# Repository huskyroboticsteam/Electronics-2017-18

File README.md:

# Electronics-2017-18

This is the 2017-18 Husky Robotics repository for electronics board designs and everything else electronics!

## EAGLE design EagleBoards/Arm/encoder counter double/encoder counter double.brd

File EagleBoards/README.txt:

Folder for the HRT Eagle library, Eagle Boards

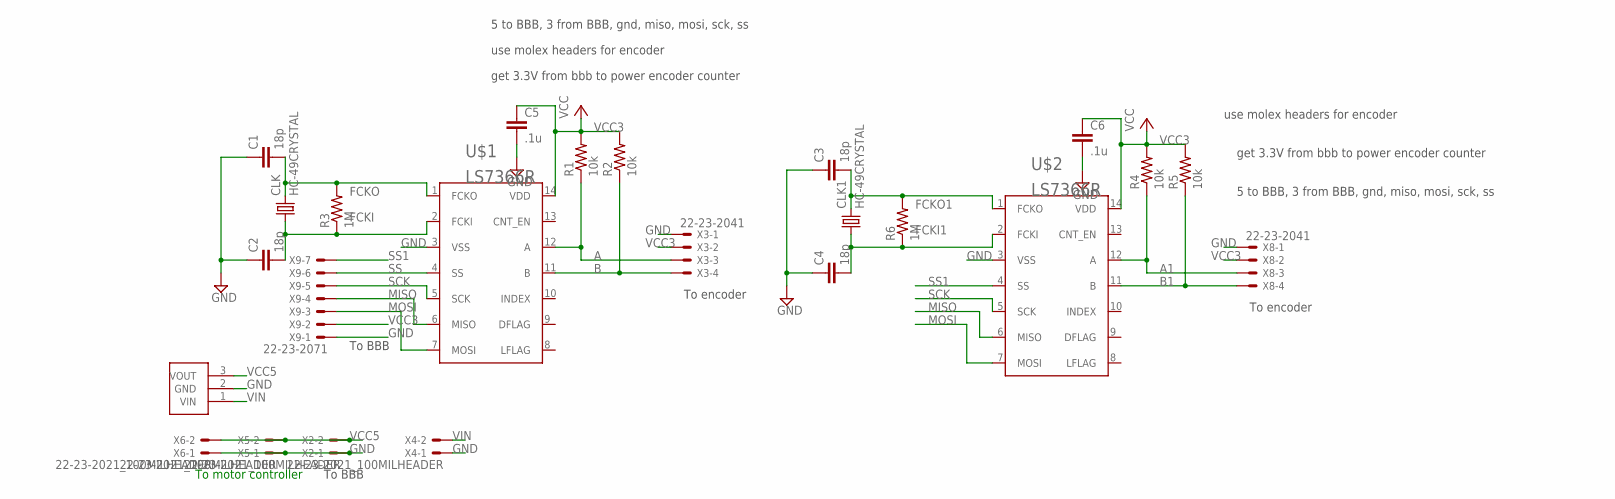
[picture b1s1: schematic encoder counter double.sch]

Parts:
C1, C2, C3, C4: 18p; C1206
C5, C6: .1u; C1206
CLK, CLK1: HC-49CRYSTAL; HC49/S
R1, R2, R4, R5: 10k; R1206
R3, R6: 1M; R1206
U$1, U$2: LS7366R; SO14
U$3: OKI-78SR-X_3PIN-DCDC; MA03-1
X2, X4, X5, X6: 22-23-2021_100MILHEADER; 22-23-2021_199MILHEADER
X3, X8: 22-23-2041
X9: 22-23-2071

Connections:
A: R1.1, U$1.12 (A), X3.3
A1: R4.1, U$2.12 (A), X8.3
B: R2.1, U$1.11 (B), X3.4
B1: R5.1, U$2.11 (B), X8.4
FCKI: C2.2, CLK.1, R3.1, U$1.2 (FCKI)
FCKI1: C4.2, CLK1.1, R6.1, U$2.2 (FCKI)
FCKO: C1.2, CLK.2, R3.2, U$1.1 (FCKO)
FCKO1: C3.2, CLK1.2, R6.2, U$2.1 (FCKO)
GND: C1.1, C2.1, C3.1, C4.1, C5.2, C6.2, U$1.3 (VSS), U$2.3 (VSS), U$3.2 (GND), X2.1, X3.1, X4.1, X5.1, X6.1, X8.1, X9.1
MISO: U$1.6 (MISO), U$2.6 (MISO), X9.4
MOSI: U$1.7 (MOSI), U$2.7 (MOSI), X9.3
SCK: U$1.5 (SCK), U$2.5 (SCK), X9.5
SS: U$1.4 (SS), X9.6
SS1: U$2.4 (SS), X9.7
VCC3: C5.1, C6.1, R1.2, R2.2, R4.2, R5.2, U$1.14 (VDD), U$2.14 (VDD), X3.2, X8.2, X9.2
VCC5: U$3.3 (VOUT), X2.2, X5.2, X6.2
VIN: U$3.1 (VIN), X4.2

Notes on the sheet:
use molex headers for encoder
get 3.3V from bbb to power encoder counter
5 to BBB, 3 from BBB, gnd, miso, mosi, sck, ss
To BBB
To encoder
To motor controller

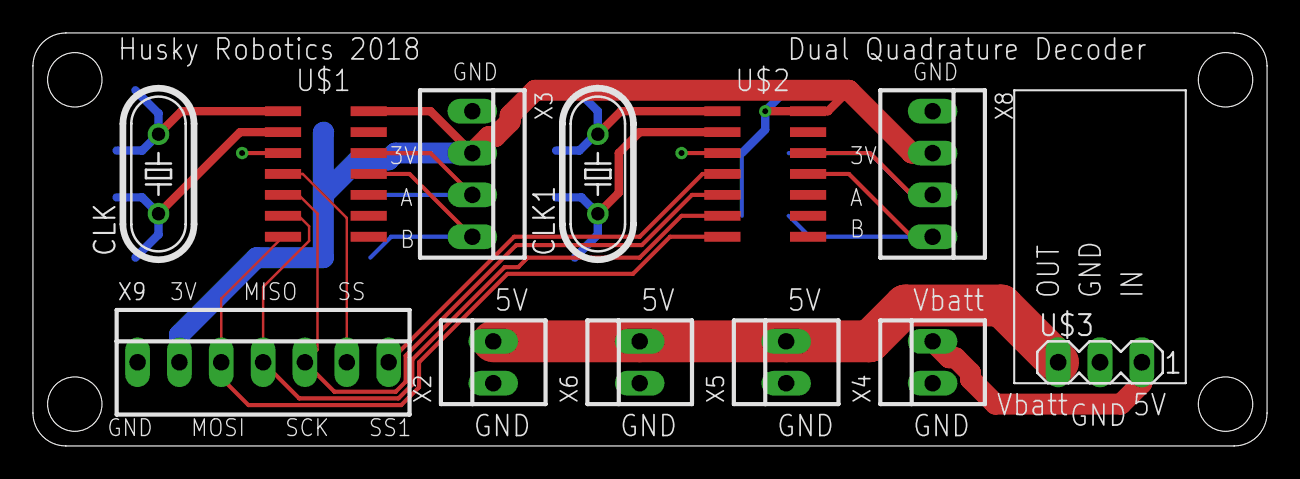
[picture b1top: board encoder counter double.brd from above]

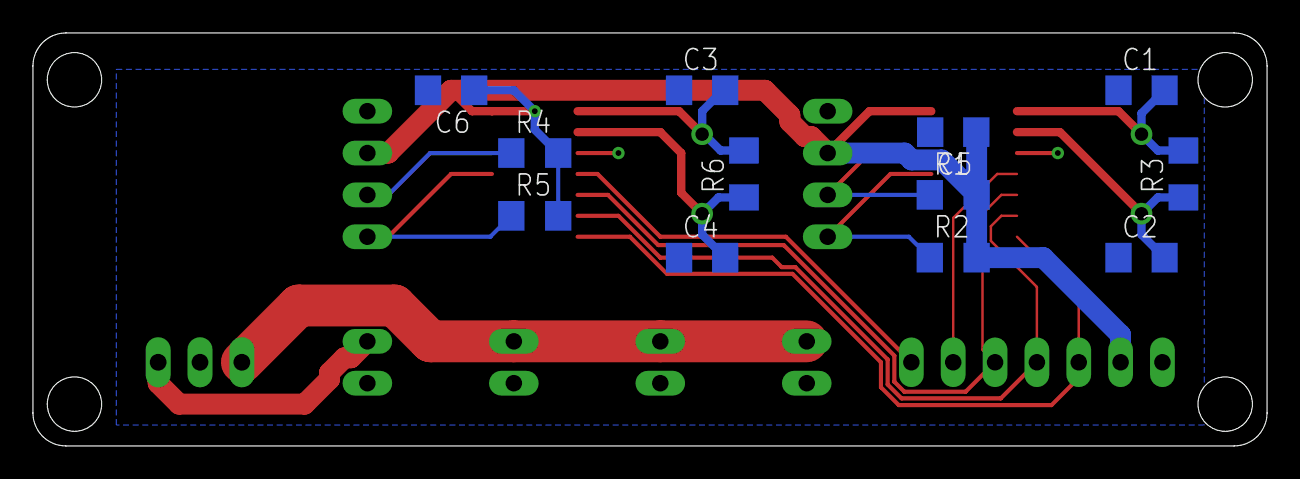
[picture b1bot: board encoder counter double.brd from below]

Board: 2 copper layers, 74.9 x 25.1 mm, 24 parts (12 on the bottom side), 17 nets.

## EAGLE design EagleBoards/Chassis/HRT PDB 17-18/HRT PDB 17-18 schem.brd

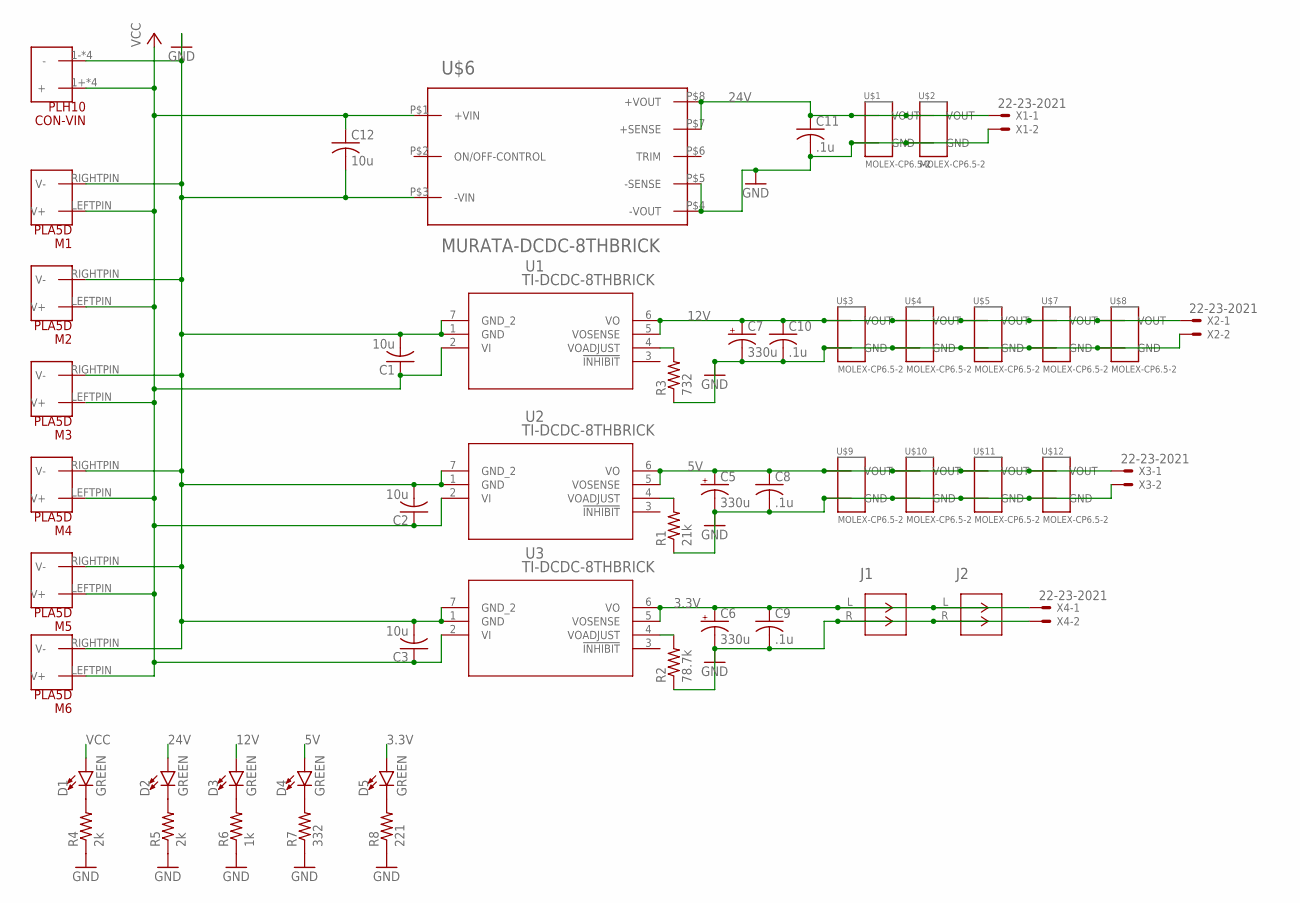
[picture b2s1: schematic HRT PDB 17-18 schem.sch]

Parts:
C1, C2, C3, C12: 10u; C1210
C5, C6, C7: 330u; E5-10,5
C8, C9, C10, C11: .1u; C0603
CON-VIN: PLH10; PLH10PCKG
D1, D2, D3, D4, D5: GREEN; LED-0603
J1, J2: TE-TERM-BLOCK
M1, M2, M3, M4, M5, M6: PLA5D; PLA5PACK
R1: 21k; R0603
R2: 78.7k; R0603
R3: 732; R0603
R4, R5: 2k; R0805
R6: 1k; R0805
R7: 332; R0805
R8: 221; R0805
U1, U2, U3: TI-DCDC-8THBRICK; TIBRICK
U$1, U$2, U$3, U$4, U$5, U$7, U$8, U$9, U$10, U$11, U$12: MOLEX-CP6.5-2; 151048-X2XX
U$6: MURATA-DCDC-8THBRICK; MURATA-8THBRICK
X1, X2, X3, X4: 22-23-2021

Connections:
3.3V: C6.+, C9.1, D5.A, J1.L (1), J2.L (1), U3.5 (VOSENSE), U3.6 (VO), X4.1
5V: C5.+, C8.1, D4.A, U2.5 (VOSENSE), U2.6 (VO), U$9.VOUT, U$10.VOUT, U$11.VOUT, U$12.VOUT, X3.1
12V: C7.+, C10.1, D3.A, U1.5 (VOSENSE), U1.6 (VO), U$3.VOUT, U$4.VOUT, U$5.VOUT, U$7.VOUT, U$8.VOUT, X2.1
24V: C11.1, D2.A, U$1.VOUT, U$2.VOUT, U$6.P$7 (+SENSE), U$6.P$8 (+VOUT), X1.1
GND: C1.2, C2.2, C3.2, C5.-, C6.-, C7.-, C8.2, C9.2, C10.2, C11.2, C12.2, CON-VIN.1- (-), CON-VIN.2- (-), CON-VIN.3- (-), CON-VIN.4- (-), J1.R (2), J2.R (2), M1.RIGHTPIN (V-), M2.RIGHTPIN (V-), M3.RIGHTPIN (V-), M4.RIGHTPIN (V-), M5.RIGHTPIN (V-), M6.RIGHTPIN (V-), R1.1, R2.1, R3.1, R4.1, R5.1, R6.1, R7.1, R8.1, U1.1 (GND), U1.7 (GND_2), U2.1 (GND), U2.7 (GND_2), U3.1 (GND), U3.7 (GND_2), U$1.GND, U$2.GND, U$3.GND, U$4.GND, U$5.GND, U$6.P$3 (-VIN), U$6.P$4 (-VOUT), U$6.P$5 (-SENSE), U$7.GND, U$8.GND, U$9.GND, U$10.GND, U$11.GND, U$12.GND, X1.2, X2.2, X3.2, X4.2
unnamed: D1.C, R4.2
unnamed: D2.C, R5.2
unnamed: R2.2, U3.4 (VOADJUST)
unnamed: R3.2, U1.4 (VOADJUST)
unnamed: R1.2, U2.4 (VOADJUST)
unnamed: D3.C, R6.2
unnamed: D4.C, R7.2
unnamed: D5.C, R8.2
VCC: C1.1, C2.1, C3.1, C12.1, CON-VIN.1+ (+), CON-VIN.2+ (+), CON-VIN.3+ (+), CON-VIN.4+ (+), D1.A, M1.LEFTPIN (V+), M2.LEFTPIN (V+), M3.LEFTPIN (V+), M4.LEFTPIN (V+), M5.LEFTPIN (V+), M6.LEFTPIN (V+), U1.2 (VI), U2.2 (VI), U3.2 (VI), U$6.P$1 (+VIN)

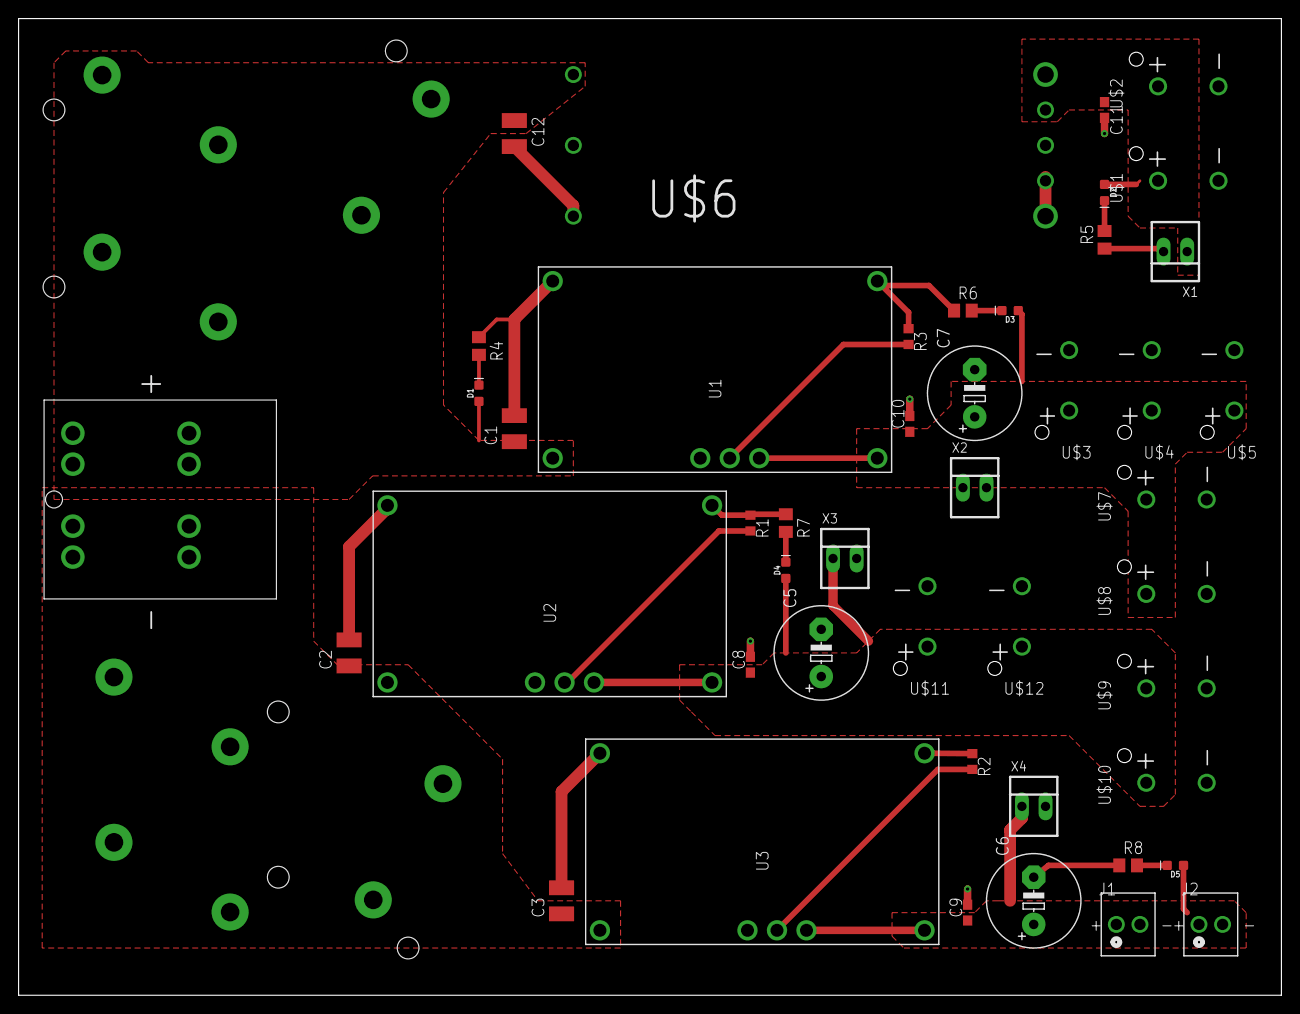
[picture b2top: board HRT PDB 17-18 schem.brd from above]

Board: 2 copper layers, 135.9 x 105.1 mm, 52 parts (0 on the bottom side), 14 nets.

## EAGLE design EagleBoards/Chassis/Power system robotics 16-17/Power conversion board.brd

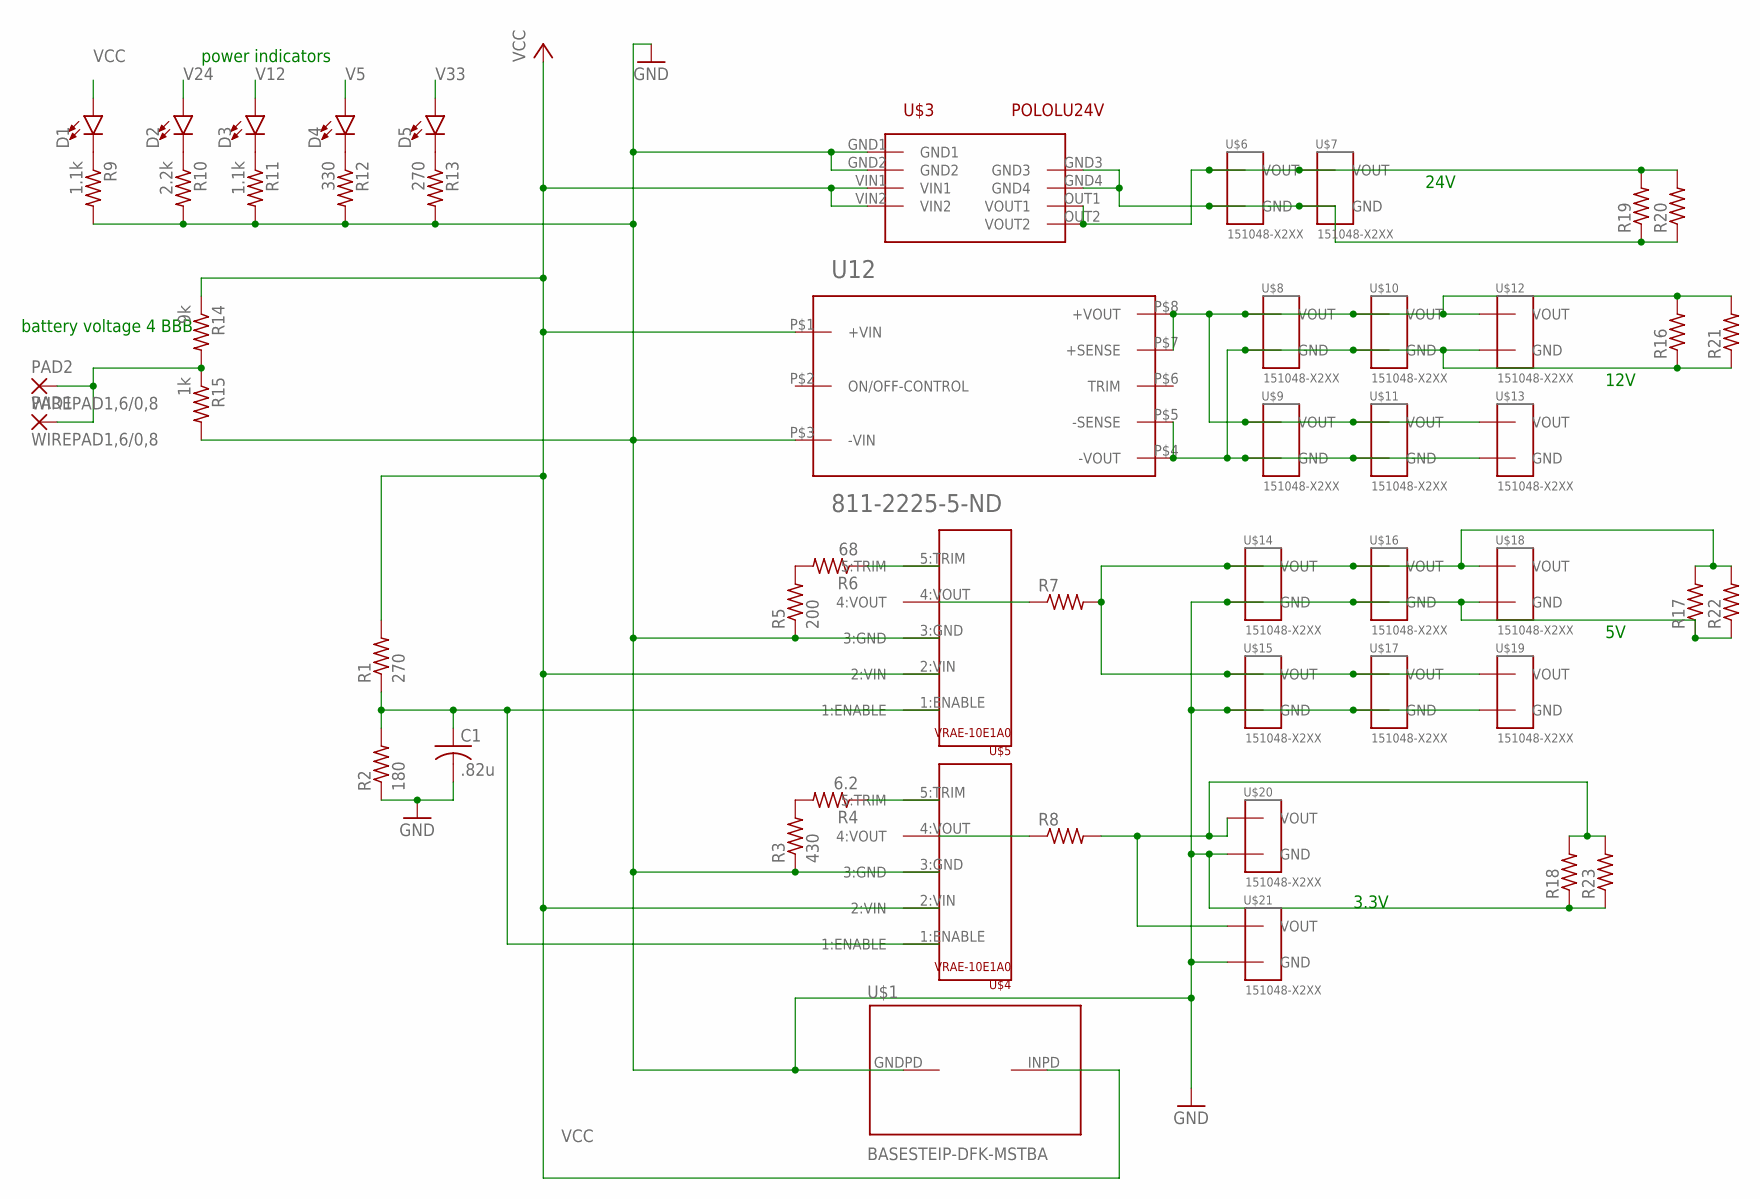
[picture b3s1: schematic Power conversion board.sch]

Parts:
C1: .82u; C0603
D1, D2, D3, D4, D5: LED5MM; LED_5MM
PAD1, PAD2: WIREPAD1,6/0,8; 1,6/0,8
R1, R13: 270; R0603
R2: 180; R0603
R3: 430; R0603
R4: 6.2; R0603
R5: 200; R0603
R6: 68; R0603
R7, R8, R16, R17, R18, R19, R20, R21, R22, R23: R-US_0204/5; 00PTCPACKAGE
R9, R11: 1.1k; R0603
R10: 2.2k; R0603
R12: 330; R0603
R14: 9k; R0603
R15: 1k; R0603
U12: 811-2225-5-ND
U$1: BASESTEIP-DFK-MSTBA; BASESTRIP-DFK-MSTBA
U$3: POLOLU24V; POLOLU24
U$4, U$5: VRAE-10E1A0; BEL_VRAE-10E1A0
U$6, U$7, U$8, U$9, U$10, U$11, U$12, U$13, U$14, U$15, U$16, U$17, U$18, U$19, U$20, U$21: 151048-X2XX

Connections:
GND: C1.2, R2.1, R3.1, R5.1, R9.2, R10.2, R11.2, R12.2, R13.2, R15.2, R16.1, R17.1, R18.1, R19.1, R20.1, R21.1, R22.1, R23.1, U12.P$3 (-VIN), U12.P$4 (-VOUT), U12.P$5 (-SENSE), U$1.GNDPD, U$3.GND1, U$3.GND2, U$3.GND3, U$3.GND4, U$4.3:GND, U$5.3:GND, U$6.GND, U$7.GND, U$8.GND, U$9.GND, U$10.GND, U$11.GND, U$12.GND, U$13.GND, U$14.GND, U$15.GND, U$16.GND, U$17.GND, U$18.GND, U$19.GND, U$20.GND, U$21.GND
unnamed: C1.1, R1.1, R2.2, U$4.1:ENABLE, U$5.1:ENABLE
unnamed: R3.2, R4.2
unnamed: R4.1, U$4.5:TRIM
unnamed: R5.2, R6.2
unnamed: R6.1, U$5.5:TRIM
unnamed: PAD1.1, PAD2.1, R14.2, R15.1
unnamed: R8.1, U$4.4:VOUT
unnamed: R7.1, U$5.4:VOUT
unnamed: D1.K (C), R9.1
unnamed: D2.K (C), R10.1
unnamed: D3.K (C), R11.1
unnamed: D4.K (C), R12.1
unnamed: D5.K (C), R13.1
V5: D4.A, R7.2, R17.2, R22.2, U$14.VOUT, U$15.VOUT, U$16.VOUT, U$17.VOUT, U$18.VOUT, U$19.VOUT
V12: D3.A, R16.2, R21.2, U12.P$7 (+SENSE), U12.P$8 (+VOUT), U$8.VOUT, U$9.VOUT, U$10.VOUT, U$11.VOUT, U$12.VOUT, U$13.VOUT
V24: D2.A, R19.2, R20.2, U$3.OUT1 (VOUT1), U$3.OUT2 (VOUT2), U$6.VOUT, U$7.VOUT
V33: D5.A, R8.2, R18.2, R23.2, U$20.VOUT, U$21.VOUT
VCC: D1.A, R1.2, R14.1, U12.P$1 (+VIN), U$1.INPD, U$3.VIN1, U$3.VIN2, U$4.2:VIN, U$5.2:VIN

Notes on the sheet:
power indicators
battery voltage 4 BBB
24V
12V
3.3V

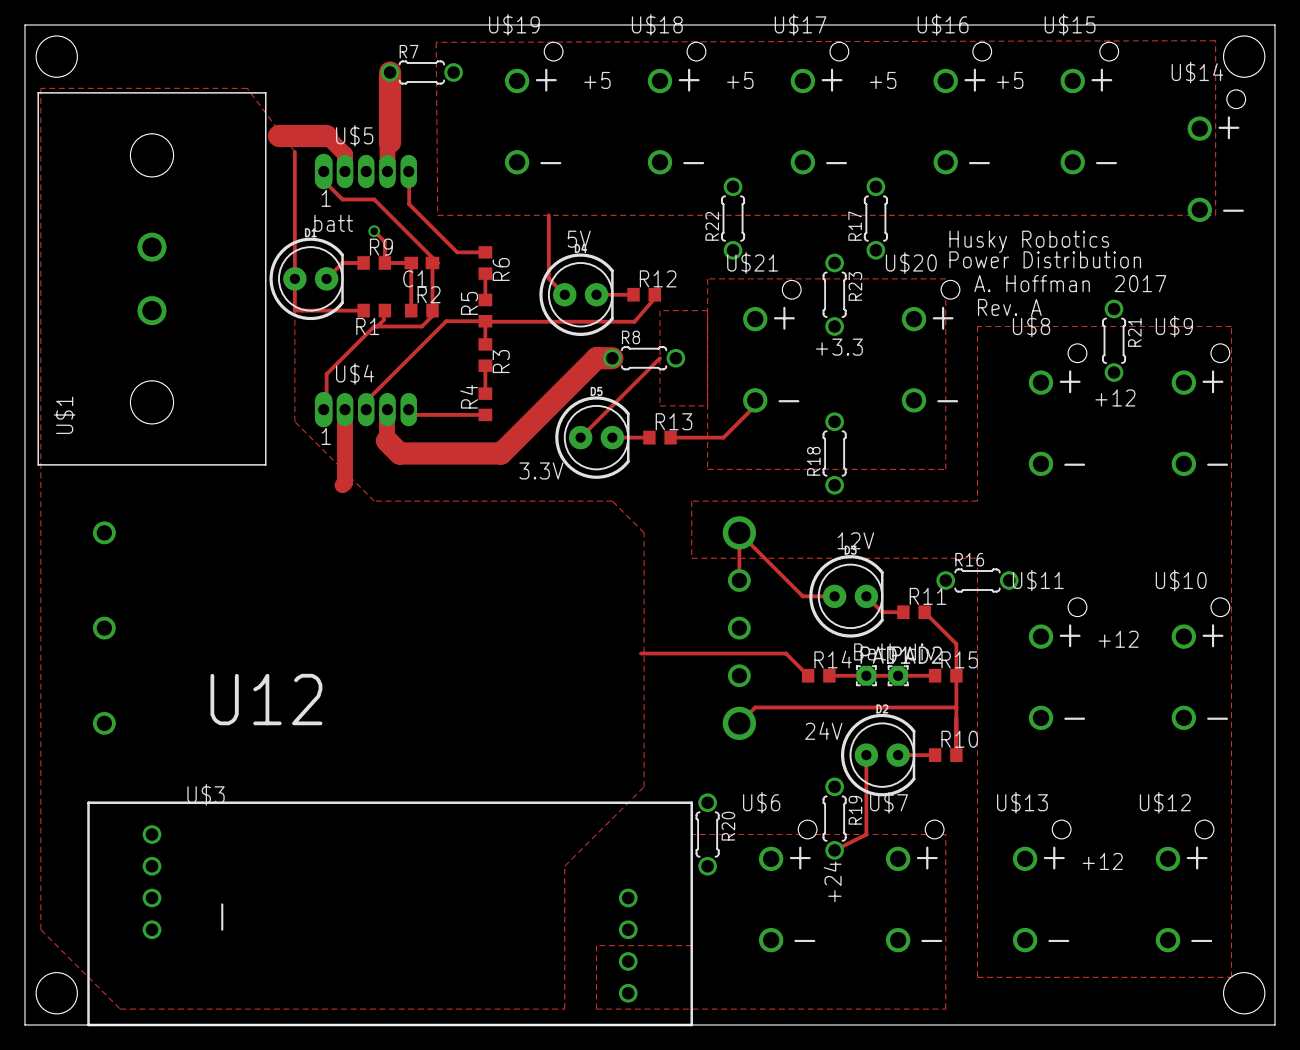
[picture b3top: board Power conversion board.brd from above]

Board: 2 copper layers, 100.0 x 80.0 mm, 52 parts (0 on the bottom side), 19 nets.

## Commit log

2017-12-02 Added empty readme
2017-12-02 Added existing Science designs.
2017-12-02 added Eagle folder
2017-12-02 Added Servo outputs
    Removed Encoder debouncing
2017-12-02 Actually saved this time
2017-12-02 Merged KiCad Libraries
    Now we have one "sciencelib" instead of 3. Releavnt changes made in schematics.
2017-12-02 Changed labelling standard for main board
2017-12-02 Current sensing on power board
2017-12-03 added eagle lbrs
2017-12-05 Added power pinouts and servo connections
2017-12-08 eagle lbr updates
2017-12-09 Changed LS7366R implementation per spec
2017-12-10 eagle gps
2017-12-23 chassis PDB in layout
2017-12-23 PDB mid dev
2017-12-23 pdb rev a
2018-01-07 Added sensor connections
2018-01-07 Added TLV2544ID to library
2018-01-07 Added ADC to main board schematic
2018-01-07 Updated schematic with new ADC layout
2018-01-07 Aded PWM device to schematic
2018-01-10 Adding component values, system current sensor
2018-01-12 Added decoupling capacitors, started component associatons, added RGB LEDs
2018-01-12 Cleaning up schematic, adding I2C test connector
2018-01-13 Fixing various board issues
    Decoupling caps, power connector, sensor connectors, power LEDs, etc.
2018-01-13 Added IC datasheets
2018-01-13 Added cable connector datasheets
2018-01-13 Fixed issues
2018-01-13 Added missing pullup
2018-01-13 Added optocouplers to servo outputs
2018-01-13 Fixed optocoupler
2018-01-13 Added connectors
2018-01-13 Added 7.2V regulator
2018-01-13 Schematic cleanup
2018-01-13 Switched to resistor networks for RGB LEDs
2018-01-13 Began Main board layout
2018-01-13 Continued working on main PCB
2018-01-14 Added BAC connectors to library
2018-01-14 Added RPi and Crystal Footprints
2018-01-14 Fixed RPi Footprint
    Someone (me) got the outline flipped...
2018-01-14 Added RGB LED footprint, working on layout
2018-01-14 Working on PCB
2018-01-14 Continuing PCB some more
2018-01-14 Began Power Board layout
2018-01-14 Added heatsink footprint
2018-01-14 Continued continuing on main board
2018-01-14 Updated footprint library
2018-01-14 "Finished routing"
    Except not really because it sucks
2018-01-14 Final PDB changes for tonight
2018-01-14 Last schematic changes for the night
2018-01-14 Finishing up for tonight.
2018-01-14 Changed layout again
    Could definitely still use some work...
2018-01-14 Finished way better layout
2018-01-14 Removed uneccessary vias
2018-01-14 Edited silkscreen
2018-01-14 Added CAD files for 3-PIN molex connector
2018-01-15 Added 4-PIN MOLEX CAD
2018-01-15 More layout
2018-01-15 Updated footprints
2018-01-15 Even more layout
2018-01-15 Added mounting holes
2018-01-15 Done for the nigtht.
    Good progress!
2018-01-15 Layout nearing completion.
2018-01-17 Small track updates
2018-01-20 Continued work on main board layout. Nearing completion!
2018-01-20 Continuing layout work
2018-01-20 Almost done
2018-01-21 Very close to finished main board
    Just needs ground plane work now!
2018-01-21 Redesign started. Looks better, although still has issues
2018-01-21 Ground planes almost done
2018-01-21 All connections made
    I think I am within spec as much as I can be. Maybe we should go with 2oz copper on this board
2018-01-21 Fixed polygon combination
2018-01-21 Last trace changes
    Will work on solder mask now
2018-01-21 Stripped away soldermask on front and back
2018-01-21 Main Board finished?
2018-01-21 Fixing issues, adding logos
2018-01-22 Fixed polygons
2018-01-22 I think the Science PDB is done
2018-01-22 Added I2C label
    (Spoke too soon)
2018-01-22 Moved a few component designators
2018-01-22 updated eagle files
2018-01-22 squeezed
2018-01-22 Final changes
    (I didn't save apparently)
2018-01-22 Replaced current sensor with INA226
2018-01-22 Forgot to save schematic changes
2018-01-23 Added Labels
    PDB is officially done
2018-01-23 Last-minute changes and production output for main board
2018-01-23 PDB production output
2018-04-15 Fixing address error
2018-06-11 encoder counter brd in layout
2018-06-29 pre silk encoder brds. layout ready for review
2018-07-02 encoder boards done
2018-07-21 printed designs with gerbers
2018-10-05 Added new board (in prog)
2018-10-05 Added UART/USB, JTAG, I2C outputs for programming
2018-10-05 Changed components
2018-10-06 Spent more time on models than I would have like to
2018-10-06 Actually added the model to the part...
2018-10-06 Saving projects isn't completely intiuitive to me yet
2018-10-06 Continuing work
2018-10-08 Worked on power for a bit

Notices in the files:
parts and their libraries:
SparkFun-LED: Licensing: Creative Commons ShareAlike 4.0 International - https://creativecommons.org/licenses/by-sa/4.0
